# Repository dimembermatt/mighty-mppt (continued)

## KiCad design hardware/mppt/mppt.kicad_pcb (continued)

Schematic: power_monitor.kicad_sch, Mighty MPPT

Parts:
C801, C802: 100n; C_0402_1005Metric_Pad0.74x0.62mm_HandSolder
IC801: INA229AIDGSR; ti_INA229_AIDGSR
NT801: NetTie_2; NetTie-2_SMD_Pad0.5mm
R801: 86.6k; R_0603_1608Metric_Pad0.98x0.95mm_HandSolder
R802: 100k; R_0603_1608Metric_Pad0.98x0.95mm_HandSolder
R803, R805: 15; R_0603_1608Metric
R804: 4m; R_Shunt_Vishay_WSKW0612
TP801, TP802: TestPoint_2Pole; TestPoint_2Pads_Pitch2.54mm_Drill0.8mm

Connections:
+3V3: C802.2, IC801.6 (VS); also elsewhere on the board
/MON_IN_CS: IC801.1 (CS); also elsewhere on the board
/MON_SPI_CIPO: IC801.4 (MISO); also elsewhere on the board
/MON_SPI_CLK: IC801.5 (SCLK); also elsewhere on the board
/MON_SPI_COPI: IC801.2 (MOSI); also elsewhere on the board
/VI+: R804.1; also elsewhere on the board
/VI-: NT801.1, R802.2, TP801.2; also elsewhere on the board
/power_converter/Load Switch Source/I+: R801.1, R804.4; also elsewhere on the board
/power_converter/Power Monitor Source/IN+: C801.2, IC801.10 (IN+), R803.1, TP802.1
/power_converter/Power Monitor Source/IN-: C801.1, IC801.9 (IN-), R805.1, TP802.2
/power_converter/Power Monitor Source/VBUS: IC801.8 (VBUS), R801.2, R802.1, TP801.1
/power_converter/~MON_ALERT: IC801.3 (ALERT); also elsewhere on the board
GND: C802.1, IC801.7 (GND), NT801.2; also elsewhere on the board
unnamed: R803.2, R804.2
unnamed: R804.3, R805.2

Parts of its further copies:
C1301, C1302: 100n; C_0402_1005Metric_Pad0.74x0.62mm_HandSolder
IC1301: INA229AIDGSR; ti_INA229_AIDGSR
NT1301: NetTie_2; NetTie-2_SMD_Pad0.5mm
R1301: 86.6k; R_0603_1608Metric_Pad0.98x0.95mm_HandSolder
R1302: 100k; R_0603_1608Metric_Pad0.98x0.95mm_HandSolder
R1303, R1305: 15; R_0603_1608Metric
R1304: 4m; R_Shunt_Vishay_WSKW0612
TP1301, TP1302: TestPoint_2Pole; TestPoint_2Pads_Pitch2.54mm_Drill0.8mm

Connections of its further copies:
+3V3: C1302.2, IC1301.6 (VS); also elsewhere on the board
/MON_OUT_CS: IC1301.1 (CS); also elsewhere on the board
/MON_SPI_CIPO: IC1301.4 (MISO); also elsewhere on the board
/MON_SPI_CLK: IC1301.5 (SCLK); also elsewhere on the board
/MON_SPI_COPI: IC1301.2 (MOSI); also elsewhere on the board
/power_converter/Load Switch Sink/I-: R1301.1, R1304.1; also elsewhere on the board
/power_converter/OUT+: R1304.4; also elsewhere on the board
/power_converter/OUT-: NT1301.1, R1302.2, TP1301.2; also elsewhere on the board
/power_converter/Power Monitor Sink/IN+: C1301.2, IC1301.10 (IN+), R1303.1, TP1302.1
/power_converter/Power Monitor Sink/IN-: C1301.1, IC1301.9 (IN-), R1305.1, TP1302.2
/power_converter/Power Monitor Sink/VBUS: IC1301.8 (VBUS), R1301.2, R1302.1, TP1301.1
/power_converter/~MON_ALERT: IC1301.3 (ALERT); also elsewhere on the board
GND: C1302.1, IC1301.7 (GND), NT1301.2; also elsewhere on the board
unnamed: R1303.2, R1304.2
unnamed: R1304.3, R1305.2

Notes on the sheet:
0-150V 158.61V max rating
106kHz -3dB cutoff
0-10.24A 15.8A max power rating

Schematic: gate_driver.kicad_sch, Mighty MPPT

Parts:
C1001, C1003, C1004: 10u; C_1206_3216Metric_Pad1.33x1.80mm_HandSolder
C1002, C1005, C1006: 100n; C_0402_1005Metric_Pad0.74x0.62mm_HandSolder
D1001, D1003: Schottky; D_SOD-123F
D1002, D1005: Zener; D_SOD-123F
D1004: 0.62V; D_SMA
NT1001: NetTie_2; NetTie-2_SMD_Pad0.5mm
Q1001: Q_NMOS_GDS; SOT-223-3_TabPin2
R1001: 100k; R_0603_1608Metric_Pad0.98x0.95mm_HandSolder
R1002, R1003, R1004, R1005: 0; R_0805_2012Metric_Pad1.20x1.40mm_HandSolder
R1006: 1.5; R_1210_3225Metric_Pad1.30x2.65mm_HandSolder
R1007: R_DT; R_0805_2012Metric_Pad1.20x1.40mm_HandSolder
U1001: ADUM4221-1ARIZ; ad_ADUM4221_1ARIZ

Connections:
+3V3: C1001.1, C1002.1, R1001.1, U1001.3 (VDD1), U1001.8 (VDD1); also elsewhere on the board
+5V: C1004.1, C1006.1, D1004.2 (A), U1001.11 (VDDB); also elsewhere on the board
/power_converter/Gate Driver/CONV_EN: Q1001.1 (G); also elsewhere on the board
/power_converter/Gate Driver/CONV_PWM: U1001.1 (PWM); also elsewhere on the board
/power_converter/Gate Driver/DISABLE: Q1001.2 (D), R1001.2, U1001.5 (DISABLE)
/power_converter/Gate Driver/DT: R1007.2, U1001.6 (DT)
/power_converter/Gate Driver/VDDA: C1003.1, C1005.1, R1006.2, U1001.16 (VDDA)
/power_converter/Gate Driver/VOA: D1003.1 (K), R1004.1, U1001.15 (VOA)
/power_converter/Gate Driver/VOB: D1001.1 (K), R1002.1, U1001.10 (VOB)
/power_converter/SWH: D1005.1 (K), R1004.2; also elsewhere on the board
/power_converter/SWL: D1002.1 (K), R1002.2; also elsewhere on the board
/power_converter/VSW: C1003.2, C1005.2, D1005.2 (A), R1005.2, U1001.14 (GNDA); also elsewhere on the board
GND: C1001.2, C1002.2, NT1001.1, Q1001.3 (S), R1007.1, U1001.4 (GND1); also elsewhere on the board
GNDPWR: C1004.2, C1006.2, D1002.2 (A), NT1001.2, R1003.2, U1001.9 (GNDB); also elsewhere on the board
unnamed: D1001.2 (A), R1003.1
unnamed: D1003.2 (A), R1005.1
unnamed: D1004.1 (K), R1006.1

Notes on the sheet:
Determine this from 0.1.0rc breakout.
Target boost range @ 55kHz Max duty: 16V to 134V D = 1 - 1/150 = 0.8806 Min duty: 75V to 80V D = 1 - 75/80 = 0.0625 T_Hmin = (1 - 0.8806) / 55kHz - 20ns = 2150.9ns T_Lmax = 0.8806 / 55kHz + 20ns = 16030.9ns T_Lmin = 0.0625 / 55kHz + 20ns = 1156.36ns Q_CB (bootstrap capacitor charge) = 7.5nC + (1603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
Overkill fet selected to consolidate BOM, consider selecting smaller and cheaper one.

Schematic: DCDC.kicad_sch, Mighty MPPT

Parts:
C501, C505: 100n; C_0805_2012Metric
C502, C506: 1u; C_2220_5750Metric
C503, C507: 2.2u; C_2220_5750Metric
C504, C508, C509: 18u; C_Radial_D10.0mm_H16.0mm_P5.00mm
D501, D503: 150; D_SMA
D502: SMAJ150CA; D_SMA
L501: 471u; ferroxcube_PQ32_20_3C97_wire
LB501: CPV-PQ32/20-1S-12PD-Z; ferroxcube_CPV-PQ32_20-1S-12P-Z
LC501: PQ32/20-3C97
LH501: CLM/P-PQ32/20
NT501: NetTie_3_Tee; NetTie-3_SMD_Pad2.0mm
Q501, Q502: EPC2059; epc_EPC2059
TP501, TP502, TP505, TP506, TP507: TestPoint; TestPoint_Keystone_5000-5004_Miniature
TP503, TP504: TestPoint_2Pole; TestPoint_2Pads_Pitch2.54mm_Drill0.8mm

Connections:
/VI-: C501.2, C502.2, C503.2, C504.2, D501.2 (A), NT501.1; also elsewhere on the board
/power_converter/Active Load Sink/V+: C505.1, C506.1, C507.1, C508.1, C509.1, D503.1 (K), Q502.3 (D), Q502.5 (D), TP504.2, TP507.1; also elsewhere on the board
/power_converter/Active Load Source/V+: C501.1, C502.1, C503.1, C504.1, D501.1 (K), L501.1, TP501.1; also elsewhere on the board
/power_converter/OUT-: C505.2, C506.2, C507.2, C508.2, C509.2, D502.1 (A1), D503.2 (A), NT501.3, Q501.2 (S), Q501.4 (S), Q501.6 (S), TP503.1, TP505.1; also elsewhere on the board
/power_converter/SWH: Q502.1 (G), TP506.1; also elsewhere on the board
/power_converter/SWL: Q501.1 (G), TP502.1; also elsewhere on the board
/power_converter/VSW: D502.2 (A2), L501.2, Q501.3 (D), Q501.5 (D), Q502.2 (S), Q502.4 (S), Q502.6 (S), TP503.2, TP504.1; also elsewhere on the board
GNDPWR: NT501.2; also elsewhere on the board

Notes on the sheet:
TRANSIENT PROTECTION
HIGH SIDE FET
SWITCH NODE
LOW SIDE FET
OUTPUT CAPACITANCE
OUTPUT RETURN
Switch selected: EPC2059 with an optimal switching frequency of 55000 Hz Input capacitors selected: Bulk caps: A759MS186M2CAAE090 x 1 HF cap: CGA9P3X7T2E225M250KA x 1 Output capacitors selected: Bulk caps: A759MS186M2CAAE090 x 2 HF cap: CGA9P3X7T2E225M250KA x 1 Input inductor selected: PQ32/20-3C97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
INPUT CAPACITANCE
OVP
OCP
INPUT
Is this sized appropriately to protect 170VDS rated FETs?
INDUCTANCE
OUTPUT
INPUT RETURN
HF Loop

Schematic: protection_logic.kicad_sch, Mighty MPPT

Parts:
C901, C902, C903, C904: 100n; C_0402_1005Metric_Pad0.74x0.62mm_HandSolder
IC901: SN74LVC08APWR; ti_SN74LVC08A_PWR
IC902: SN74LVC1G04DBVR; ti_SN74LVC1G04_DBVR
IC903: SN74HCS367PWR; ti_SN74HCS367_PWR
IC904: SN74LVC2G32DCUR; ti_SN74LVC2G32_DCUR
R901, R902, R903, R904, R905, R906, R907: 100k; R_0603_1608Metric_Pad0.98x0.95mm_HandSolder
TP901, TP902, TP903, TP904, TP905, TP906: TestPoint_Small; TestPoint_Pad_D1.0mm

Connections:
+3V3: C901.1, C902.1, C903.1, C904.1, IC901.14 (VCC), IC902.5 (VCC), IC903.16 (VCC), IC904.8 (VCC), R901.1, R902.1, R904.1; also elsewhere on the board
/AL_IN_EN: IC904.2 (1B); also elsewhere on the board
/AL_OUT_EN: IC904.6 (2B); also elsewhere on the board
/CONV_DISABLE: IC903.15 (~2OE); also elsewhere on the board
/CONV_EN: IC901.10 (3B); also elsewhere on the board
/CONV_PWM: IC903.14 (2A2); also elsewhere on the board
/LS_IN_EN: IC901.2 (1B); also elsewhere on the board
/LS_OUT_EN: IC901.5 (2B); also elsewhere on the board
/MON_ALERT: IC902.4 (Y), IC904.1 (1A), IC904.5 (2A); also elsewhere on the board
/PROT_DISABLE: IC903.1 (~1OE); also elsewhere on the board
/power_converter/AL_SNK_EN_BUF: IC903.9 (1Y4), R902.2, TP901.1; also elsewhere on the board
/power_converter/AL_SRC_EN_BUF: IC903.7 (1Y3), R904.2, TP903.1; also elsewhere on the board
/power_converter/Gate Driver/CONV_EN: IC903.11 (2Y1), R906.1, TP905.1; also elsewhere on the board
/power_converter/Gate Driver/CONV_PWM: IC903.13 (2Y2), R907.1, TP906.1; also elsewhere on the board
/power_converter/LS_SNK_EN_BUF: IC903.5 (1Y2), R905.1, TP904.1; also elsewhere on the board
/power_converter/LS_SRC_EN_BUF: IC903.3 (1Y1), R903.1, TP902.1; also elsewhere on the board
/power_converter/Protection Logic/AL_SNK_EN_OR: IC903.10 (1A4), IC904.7 (1Y)
/power_converter/Protection Logic/AL_SRC_EN_OR: IC903.6 (1A3), IC904.3 (2Y)
/power_converter/Protection Logic/CONV_EN_AND: IC901.8 (3Y), IC903.12 (2A1)
/power_converter/Protection Logic/LS_SNK_EN_AND: IC901.6 (2Y), IC903.4 (1A2)
/power_converter/Protection Logic/LS_SRC_EN_AND: IC901.3 (1Y), IC903.2 (1A1)
/power_converter/~MON_ALERT: IC901.1 (1A), IC901.4 (2A), IC901.9 (3A), IC902.2 (A), R901.2; also elsewhere on the board
GND: C901.2, C902.2, C903.2, C904.2, IC901.7 (GND), IC901.11 (4Y), IC901.12 (4A), IC901.13 (4B), IC902.3 (GND), IC903.8 (GND), IC904.4 (GND), R903.2, R905.2, R906.2, R907.2; also elsewhere on the board

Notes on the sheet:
DISABLE used for logic testing. Tie to GND for final design.
Schmitt Trigger Buffer.
OR logic.
AND logic.
Open drain wired-OR.
NOT logic.

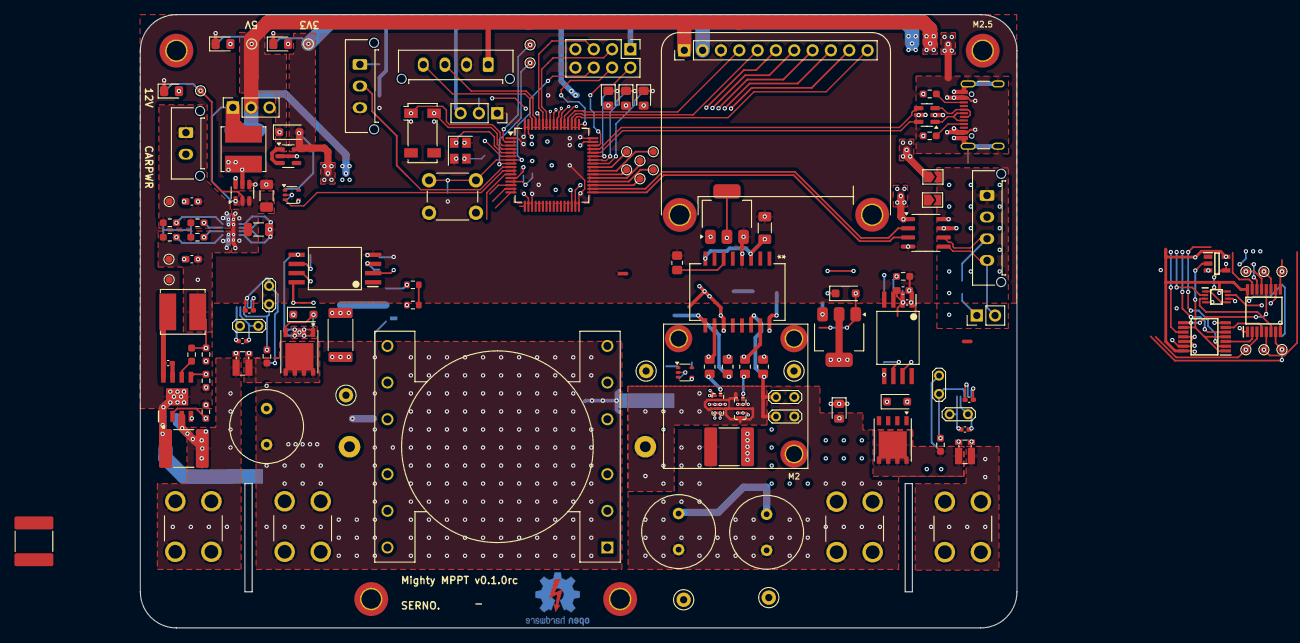
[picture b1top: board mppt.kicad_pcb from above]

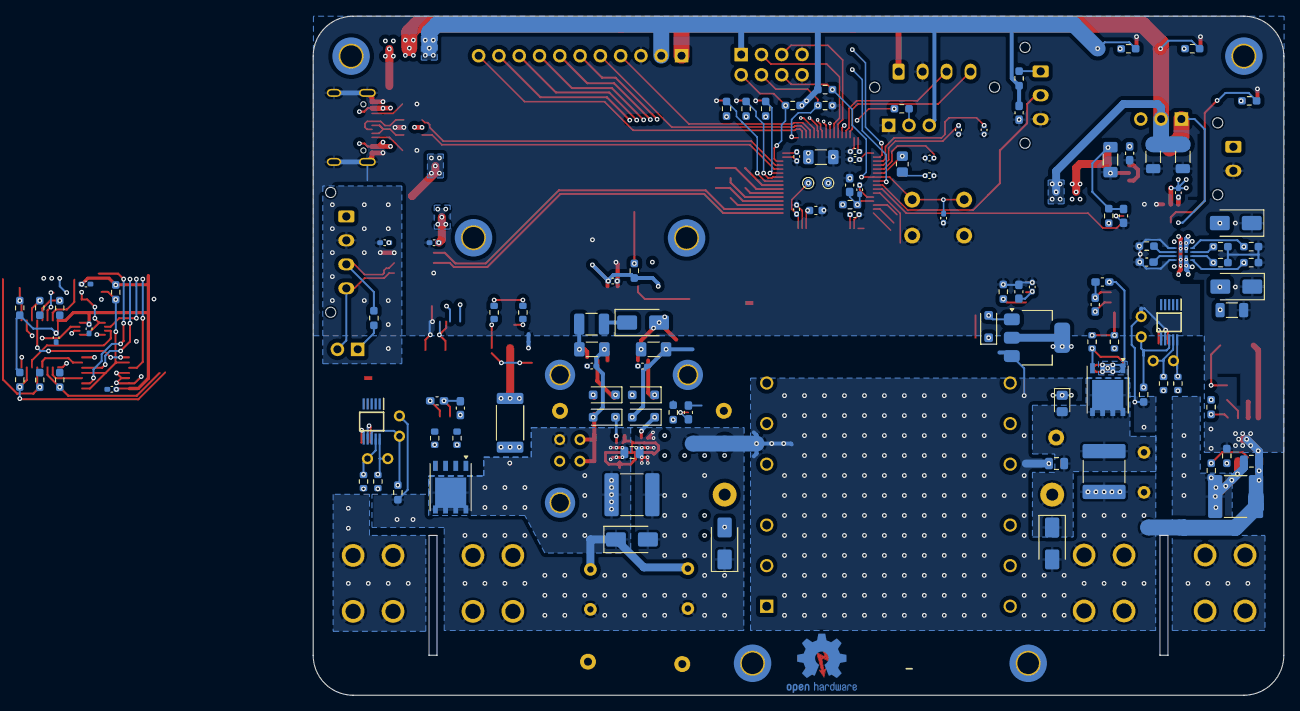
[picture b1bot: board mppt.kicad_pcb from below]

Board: 4 copper layers, 121.5 x 85.0 mm, 257 parts (119 on the bottom side), 161 nets.

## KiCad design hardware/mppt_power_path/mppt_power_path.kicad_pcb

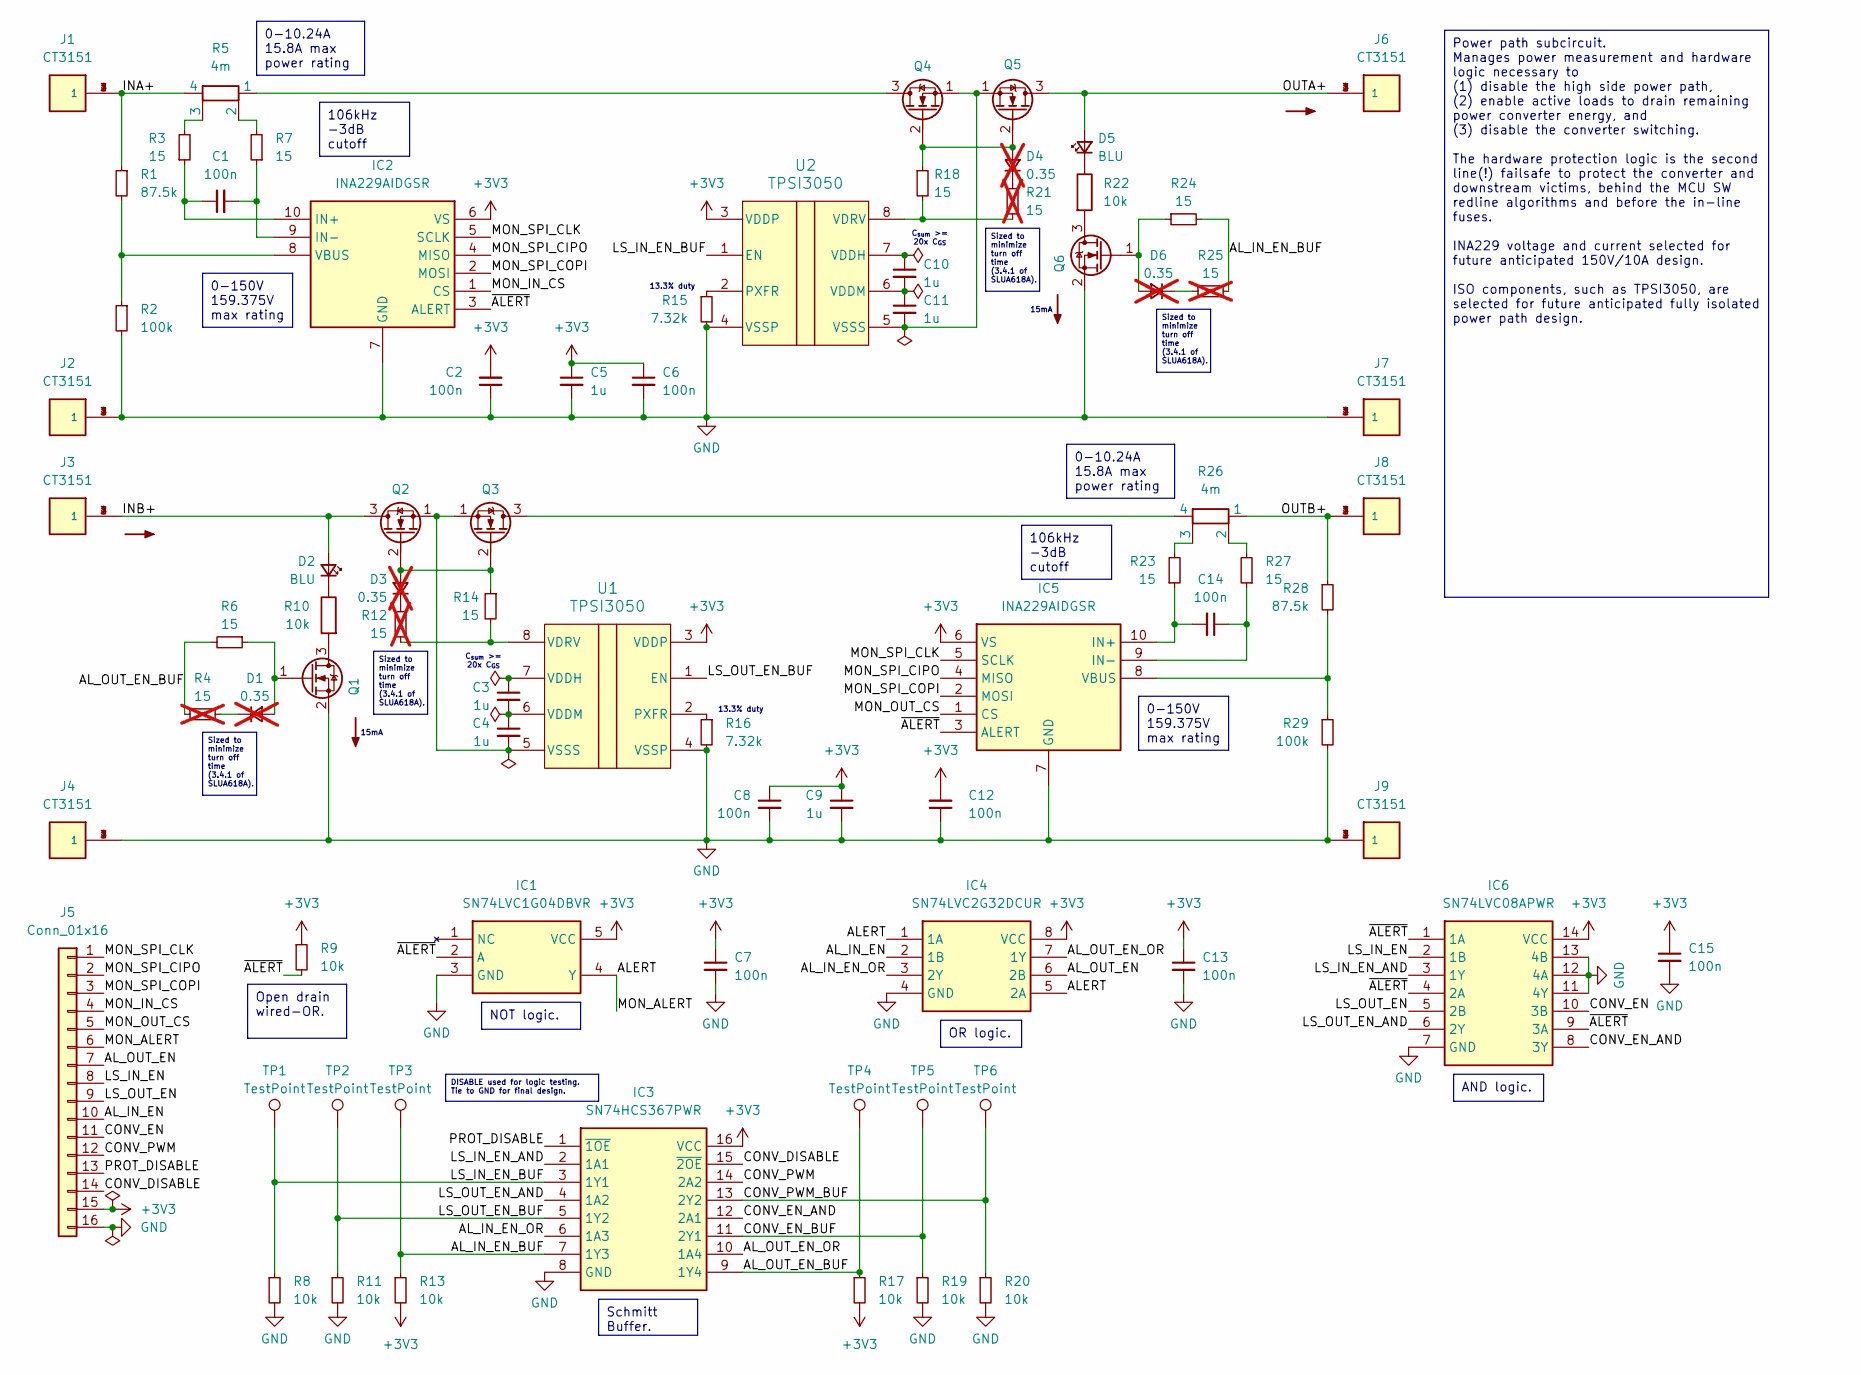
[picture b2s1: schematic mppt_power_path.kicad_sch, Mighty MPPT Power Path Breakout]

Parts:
C1, C2, C6, C7, C8, C12, C13, C14, C15: 100n; C_0805_2012Metric_Pad1.18x1.45mm_HandSolder
C3, C4, C5, C9, C10, C11: 1u; C_0805_2012Metric_Pad1.18x1.45mm_HandSolder
D1, D3, D4, D6: 0.35; D_SOD-123F; not fitted
D2, D5: BLU; LED_0805_2012Metric_Pad1.15x1.40mm_HandSolder
IC1: SN74LVC1G04DBVR; ti_SN74LVC1G04_DBVR
IC2, IC5: INA229AIDGSR; ti_INA229_AIDGSR
IC3: SN74HCS367PWR; ti_SN74HCS367_PWR
IC4: SN74LVC2G32DCUR; ti_SN74LVC2G32_DCUR
IC6: SN74LVC08APWR; ti_SN74LVC08A_PWR
J1, J2, J3, J4, J6, J7, J8, J9: CT3151; caltest_ct3151
J5: Conn_01x16; PinHeader_1x16_P2.54mm_Vertical
Q1, Q6: Q_NMOS_GSD; SOT-23-3
Q2, Q3, Q4, Q5: Q_NMOS_SGD; PowerPAK_SO-8_Single
R1, R28: 87.5k; R_0805_2012Metric_Pad1.20x1.40mm_HandSolder
R2, R29: 100k; R_0805_2012Metric_Pad1.20x1.40mm_HandSolder
R3, R6, R7, R14, R18, R23, R24, R27: 15; R_0805_2012Metric_Pad1.20x1.40mm_HandSolder
R4, R12, R21, R25: 15; R_0805_2012Metric_Pad1.20x1.40mm_HandSolder; not fitted
R5, R26: 4m; R_Shunt_Vishay_WSKW0612
R8, R9, R11, R13, R17, R19, R20: 10k; R_0805_2012Metric_Pad1.20x1.40mm_HandSolder
R10, R22: 10k; R_2512_6332Metric_Pad1.40x3.35mm_HandSolder
R15, R16: 7.32k; R_0805_2012Metric_Pad1.20x1.40mm_HandSolder
TP1, TP2, TP3, TP4, TP5, TP6: TestPoint; TestPoint_Keystone_5000-5004_Miniature
U1, U2: TPSI3050; ti_TPS3050_DWZ

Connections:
+3V3: C2.2, C5.1, C6.1, C7.1, C8.1, C9.1, C12.2, C13.1, C15.1, IC1.5 (VCC), IC2.6 (VS), IC3.16 (VCC), IC4.8 (VCC), IC5.6 (VS), IC6.14 (VCC), J5.15, R9.1, R13.2, R17.2, U1.3 (VDDP), U2.3 (VDDP)
/ALERT: IC1.4 (Y), IC4.1 (1A), IC4.5 (2A), J5.6
/AL_IN_EN: IC4.2 (1B), J5.10
/AL_IN_EN_BUF: IC3.7 (1Y3), R13.1, R24.2, R25.2, TP3.1
/AL_IN_EN_OR: IC3.6 (1A3), IC4.3 (2Y)
/AL_OUT_EN: IC4.6 (2B), J5.7
/AL_OUT_EN_BUF: IC3.9 (1Y4), R4.2, R6.2, R17.1, TP4.1
/AL_OUT_EN_OR: IC3.10 (1A4), IC4.7 (1Y)
/CONV_DISABLE: IC3.15 (~2OE), J5.14
/CONV_EN: IC6.10 (3B), J5.11
/CONV_EN_AND: IC3.12 (2A1), IC6.8 (3Y)
/CONV_EN_BUF: IC3.11 (2Y1), R19.1, TP5.1
/CONV_PWM: IC3.14 (2A2), J5.12
/CONV_PWM_BUF: IC3.13 (2Y2), R20.1, TP6.1
/INA+: J1.1, J1.2 (1), J1.3 (1), J1.4 (1), R1.1, R5.4
/INB+: D2.2 (A), J3.1, J3.2 (1), J3.3 (1), J3.4 (1), Q2.3 (D)
/LS_IN_EN: IC6.2 (1B), J5.8
/LS_IN_EN_AND: IC3.2 (1A1), IC6.3 (1Y)
/LS_IN_EN_BUF: IC3.3 (1Y1), R8.1, TP1.1, U2.1 (EN)
/LS_OUT_EN: IC6.5 (2B), J5.9
/LS_OUT_EN_AND: IC3.4 (1A2), IC6.6 (2Y)
/LS_OUT_EN_BUF: IC3.5 (1Y2), R11.1, TP2.1, U1.1 (EN)
/MON_IN_CS: IC2.1 (CS), J5.4
/MON_OUT_CS: IC5.1 (CS), J5.5
/MON_SPI_CIPO: IC2.4 (MISO), IC5.4 (MISO), J5.2
/MON_SPI_CLK: IC2.5 (SCLK), IC5.5 (SCLK), J5.1
/MON_SPI_COPI: IC2.2 (MOSI), IC5.2 (MOSI), J5.3
/OUTA+: D5.2 (A), J6.1, J6.2 (1), J6.3 (1), J6.4 (1), Q5.3 (D)
/OUTB+: J8.1, J8.2 (1), J8.3 (1), J8.4 (1), R26.1, R28.1
/PROT_DISABLE: IC3.1 (~1OE), J5.13
/~ALERT: IC1.2 (A), IC2.3 (ALERT), IC5.3 (ALERT), IC6.1 (1A), IC6.4 (2A), IC6.9 (3A), R9.2
GND: C2.1, C5.2, C6.2, C7.2, C8.2, C9.2, C12.1, C13.2, C15.2, IC1.3 (GND), IC2.7 (GND), IC3.8 (GND), IC4.4 (GND), IC5.7 (GND), IC6.7 (GND), IC6.11 (4Y), IC6.12 (4A), IC6.13 (4B), J2.1, J2.2 (1), J2.3 (1), J2.4 (1), J4.1, J4.2 (1), J4.3 (1), J4.4 (1), J5.16, J7.1, J7.2 (1), J7.3 (1), J7.4 (1), J9.1, J9.2 (1), J9.3 (1), J9.4 (1), Q1.2 (S), Q6.2 (S), R2.2, R8.2, R11.2, R15.2, R16.2, R19.2, R20.2, R29.2, U1.4 (VSSP), U2.4 (VSSP)
unnamed: D1.2 (A), Q1.1 (G), R6.1
unnamed: D1.1 (K), R4.1
unnamed: D2.1 (K), R10.1
unnamed: D3.2 (A), Q2.2 (G), Q3.2 (G), R14.1
unnamed: D3.1 (K), R12.1
unnamed: D4.2 (A), Q4.2 (G), Q5.2 (G), R18.1
unnamed: D4.1 (K), R21.1
unnamed: D5.1 (K), R22.1
unnamed: D6.2 (A), Q6.1 (G), R24.1
unnamed: D6.1 (K), R25.1
unnamed: C1.1, IC2.10 (IN+), R3.1
unnamed: C1.2, IC2.9 (IN-), R7.1
unnamed: IC2.8 (VBUS), R1.2, R2.1
unnamed: C14.2, IC5.10 (IN+), R23.1
unnamed: C14.1, IC5.9 (IN-), R27.1
unnamed: IC5.8 (VBUS), R28.2, R29.1
unnamed: Q1.3 (D), R10.2
unnamed: C4.2, Q2.1 (S), Q3.1 (S), U1.5 (VSSS)
unnamed: Q3.3 (D), R26.4
unnamed: Q4.3 (D), R5.1
unnamed: C11.2, Q4.1 (S), Q5.1 (S), U2.5 (VSSS)
unnamed: Q6.3 (D), R22.2
unnamed: R3.2, R5.3
unnamed: R5.2, R7.2
unnamed: R23.2, R26.3
unnamed: R26.2, R27.2
unnamed: R16.1, U1.2 (PXFR)
unnamed: C3.1, U1.7 (VDDH)
unnamed: C3.2, C4.1, U1.6 (VDDM)
unnamed: R12.2, R14.2, U1.8 (VDRV)
unnamed: R15.1, U2.2 (PXFR)
unnamed: C10.1, U2.7 (VDDH)
unnamed: C10.2, C11.1, U2.6 (VDDM)
unnamed: R18.2, R21.2, U2.8 (VDRV)

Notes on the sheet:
Sized to minimize turn off time (3.4.1 of SLUA618A).
0-150V 159.375V max rating
0-10.24A 15.8A max power rating
NOT logic.
Schmitt Buffer.
Open drain wired-OR.
106kHz -3dB cutoff
Power path subcircuit. Manages power measurement and hardware logic necessary to (1) disable the high side power path, (2) enable active loads to drain remaining power converter energy, and (3) disable the converter switching. The hardware protection logic is the second line(!) failsafe to protect 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
OR logic.
AND logic.
DISABLE used for logic testing. Tie to GND for final design.
C_{sum} >= 20x C_{GS}
13.3% duty
15mA

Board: 2 copper layers, 79 parts (4 on the bottom side), 66 nets, no tracks yet.

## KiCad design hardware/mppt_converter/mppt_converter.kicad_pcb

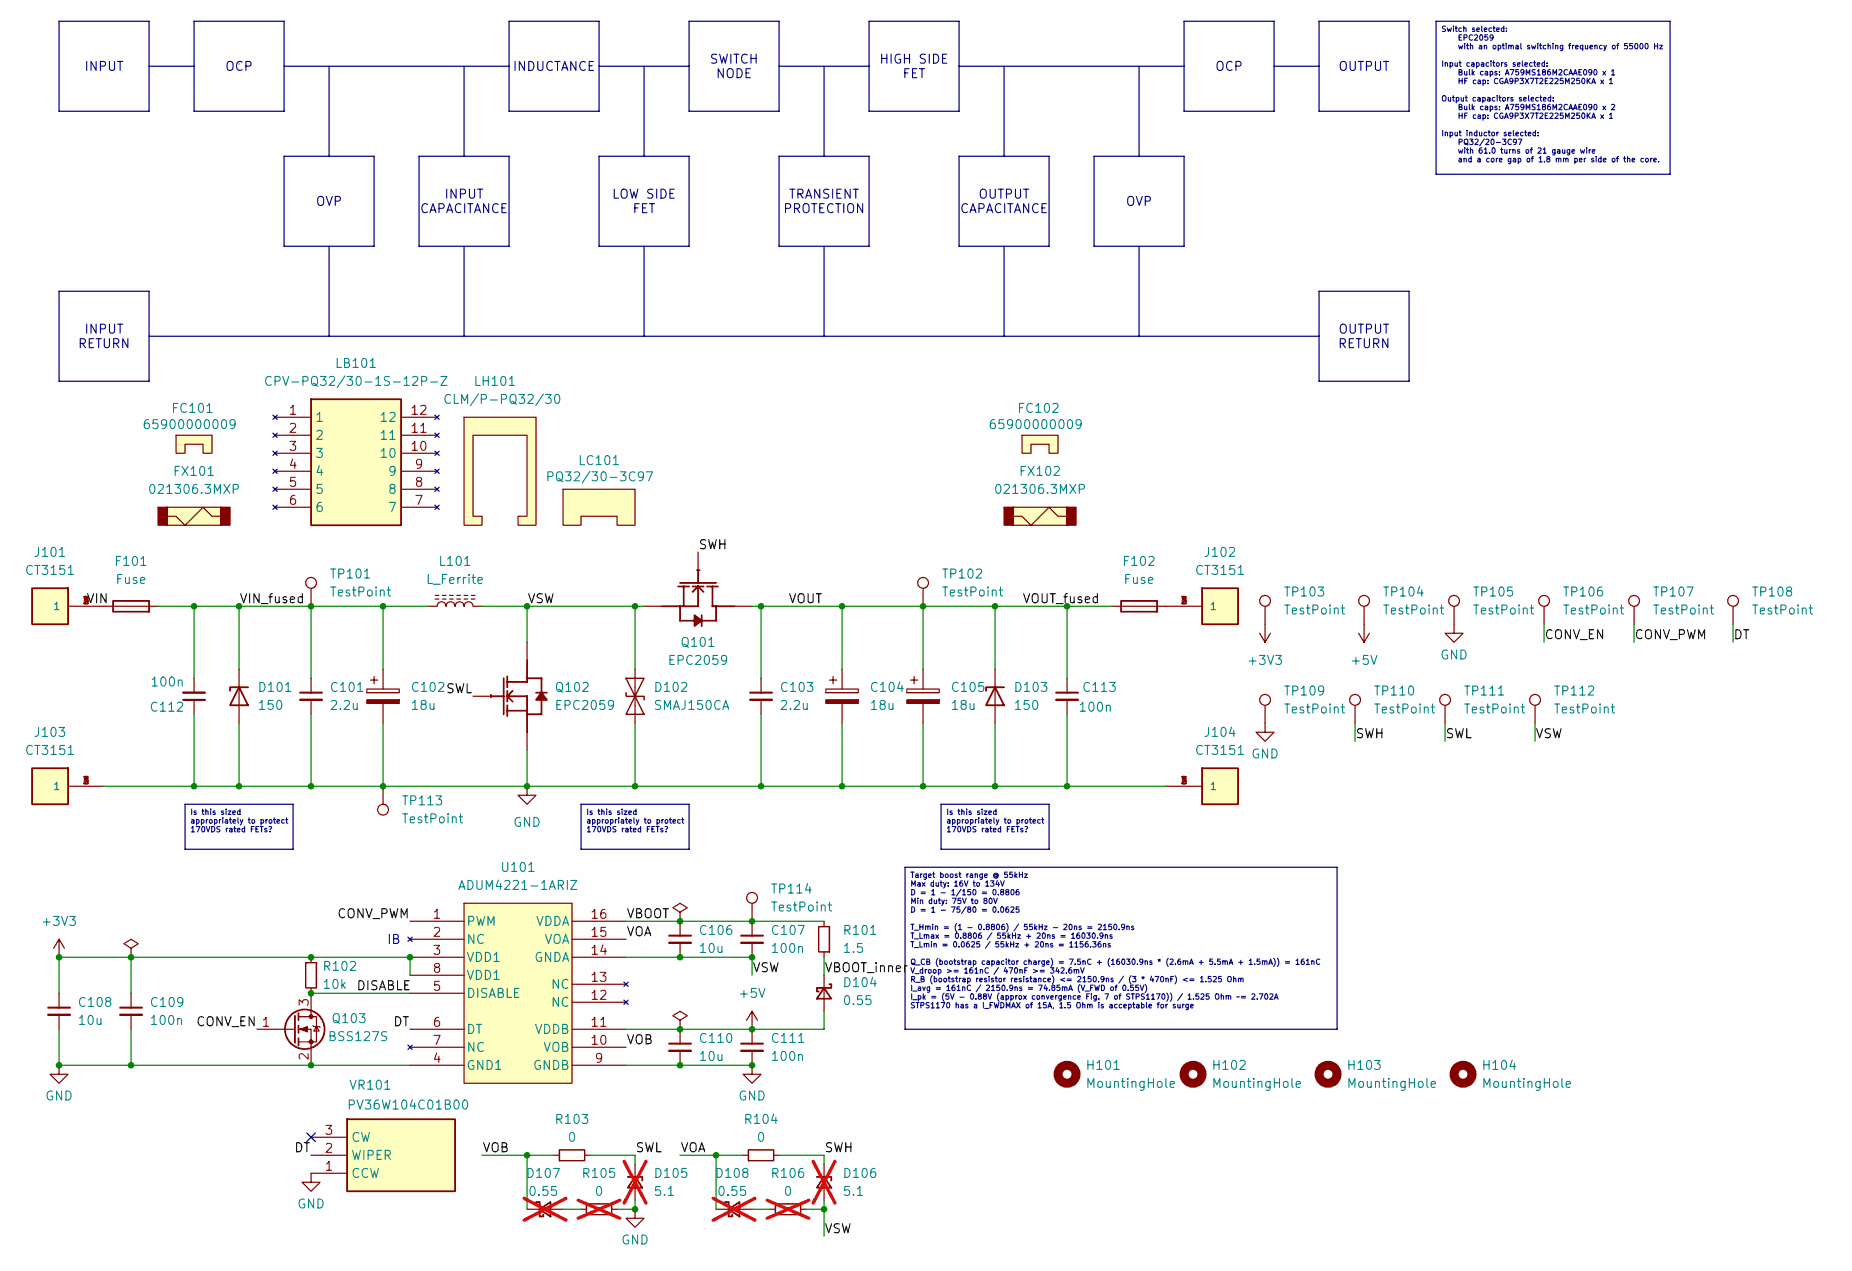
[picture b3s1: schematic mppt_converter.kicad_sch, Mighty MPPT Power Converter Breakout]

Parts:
C101, C103: 2.2u; C_2220_5750Metric_Pad1.97x5.40mm_HandSolder
C102, C104, C105: 18u; C_Radial_D10.0mm_H16.0mm_P5.00mm
C106, C108, C110: 10u; C_0805_2012Metric_Pad1.18x1.45mm_HandSolder
C107, C109, C111, C112, C113: 100n; C_0805_2012Metric_Pad1.18x1.45mm_HandSolder
D101, D103: 150; D_SMA
D102: SMAJ150CA; D_SMA
D104: 0.55; stm_STPS1170AF
D105, D106: 5.1; D_SOD-123; not fitted
D107, D108: 0.55; stm_STPS1170AF; not fitted
F101, F102: Fuse; littelfuse_65600001009
FC101, FC102: 65900000009
FX101, FX102: 021306.3MXP
H101, H102, H103, H104: MountingHole; MountingHole_5.3mm_M5
J101, J102, J103, J104: CT3151; caltest_ct3151
L101: L_Ferrite; ferroxcube_PQ32_30_3C97_wire
LB101: CPV-PQ32/30-1S-12P-Z; ferroxcube_CPV-PQ32_30-1S-12P-Z
LC101: PQ32/30-3C97
LH101: CLM/P-PQ32/30
Q101, Q102: EPC2059; epc_EPC2059
Q103: BSS127S; SOT-23
R101: 1.5; R_0805_2012Metric_Pad1.20x1.40mm_HandSolder
R102: 10k; R_0805_2012Metric_Pad1.20x1.40mm_HandSolder
R103, R104: 0; R_0805_2012Metric_Pad1.20x1.40mm_HandSolder
R105, R106: 0; R_0805_2012Metric_Pad1.20x1.40mm_HandSolder; not fitted
TP101, TP102, TP103, TP104, TP105, TP106, TP107, TP108, TP109, TP110, TP111, TP112, TP113, TP114: TestPoint; TestPoint_Keystone_5000-5004_Miniature
U101: ADUM4221-1ARIZ; ad_ADUM4221_1ARIZ
VR101: PV36W104C01B00; bourns_PV36W201C01B00

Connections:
+3V3: C108.1, C109.1, R102.1, TP103.1, U101.3 (VDD1), U101.8 (VDD1)
+5V: C110.1, C111.1, D104.2 (A), TP104.1, U101.11 (VDDB)
/CONV_EN: Q103.1 (G), TP106.1
/CONV_PWM: TP107.1, U101.1 (PWM)
/DISABLE: Q103.3 (D), R102.2, U101.5 (DISABLE)
/DT: TP108.1, U101.6 (DT), VR101.2 (WIPER)
/SWH: D106.1 (K), Q101.1 (G), R104.2, TP110.1
/SWL: D105.1 (K), Q102.1 (G), R103.2, TP111.1
/VBOOT: C106.1, C107.1, R101.2, TP114.1, U101.16 (VDDA)
/VBOOT_inner: D104.1 (K), R101.1
/VIN_fused: C101.1, C102.1, C112.2, D101.1 (K), F101.2, L101.1, TP101.1
/VOA: D108.1 (K), R104.1, U101.15 (VOA)
/VOB: D107.1 (K), R103.1, U101.10 (VOB)
/VOUT: C103.1, C104.1, C105.1, C113.1, D103.1 (K), F102.1, Q101.3 (D), Q101.5 (D), TP102.1
/VSW: C106.2, C107.2, D102.2 (A2), D106.2 (A), L101.2, Q101.2 (S), Q101.4 (S), Q101.6 (S), Q102.3 (D), Q102.5 (D), R106.2, TP112.1, U101.14 (GNDA)
GND: C101.2, C102.2, C103.2, C104.2, C105.2, C108.2, C109.2, C110.2, C111.2, C112.1, C113.2, D101.2 (A), D102.1 (A1), D103.2 (A), D105.2 (A), J103.1, J103.2 (1), J103.3 (1), J103.4 (1), J104.1, J104.2 (1), J104.3 (1), J104.4 (1), Q102.2 (S), Q102.4 (S), Q102.6 (S), Q103.2 (S), R105.2, TP105.1, TP109.1, TP113.1, U101.4 (GND1), U101.9 (GNDB), VR101.1 (CCW)
unnamed: D107.2 (A), R105.1
unnamed: D108.2 (A), R106.1
unnamed: F101.1, J101.1, J101.2 (1), J101.3 (1), J101.4 (1)
unnamed: F102.2, J102.1, J102.2 (1), J102.3 (1), J102.4 (1)

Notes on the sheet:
Switch selected: EPC2059 with an optimal switching frequency of 55000 Hz Input capacitors selected: Bulk caps: A759MS186M2CAAE090 x 1 HF cap: CGA9P3X7T2E225M250KA x 1 Output capacitors selected: Bulk caps: A759MS186M2CAAE090 x 2 HF cap: CGA9P3X7T2E225M250KA x 1 Input inductor selected: PQ32/20-3C97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
OUTPUT
OVP
TRANSIENT PROTECTION
OCP
OUTPUT CAPACITANCE
LOW SIDE FET
Is this sized appropriately to protect 170VDS rated FETs?
SWITCH NODE
Target boost range @ 55kHz Max duty: 16V to 134V D = 1 - 1/150 = 0.8806 Min duty: 75V to 80V D = 1 - 75/80 = 0.0625 T_Hmin = (1 - 0.8806) / 55kHz - 20ns = 2150.9ns T_Lmax = 0.8806 / 55kHz + 20ns = 16030.9ns T_Lmin = 0.0625 / 55kHz + 20ns = 1156.36ns Q_CB (bootstrap capacitor charge) = 7.5nC + (1603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
OUTPUT RETURN
HIGH SIDE FET
INDUCTANCE
INPUT CAPACITANCE
INPUT RETURN
INPUT

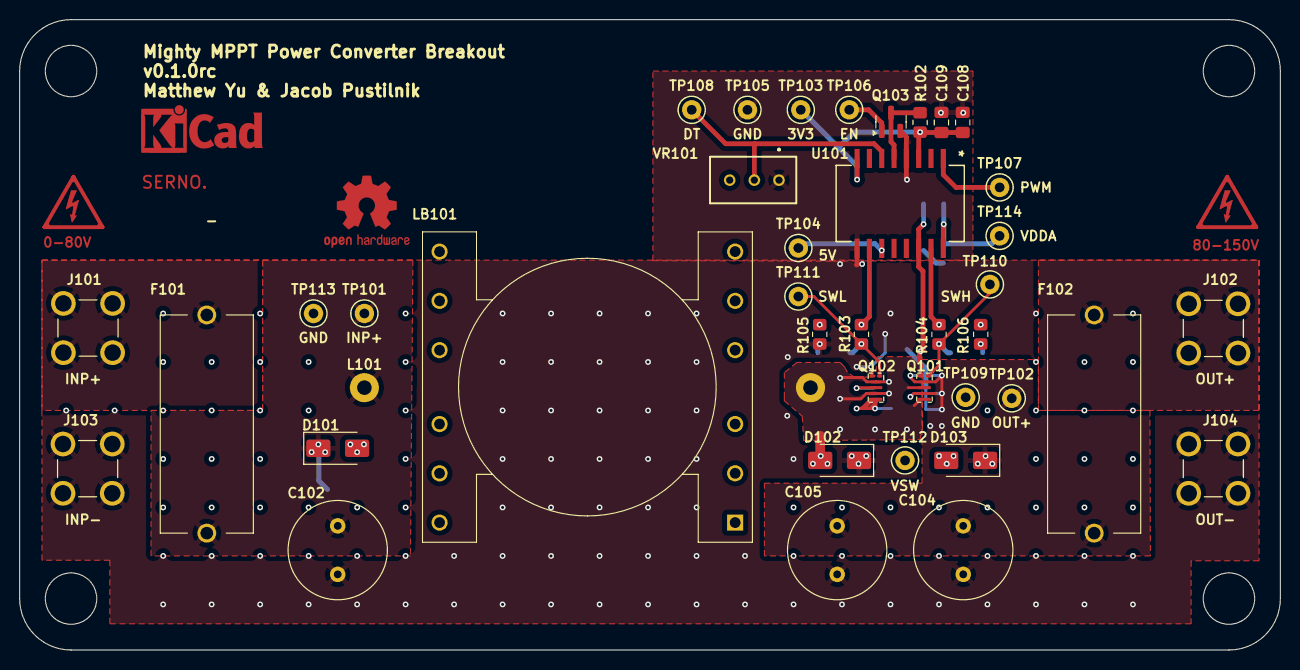
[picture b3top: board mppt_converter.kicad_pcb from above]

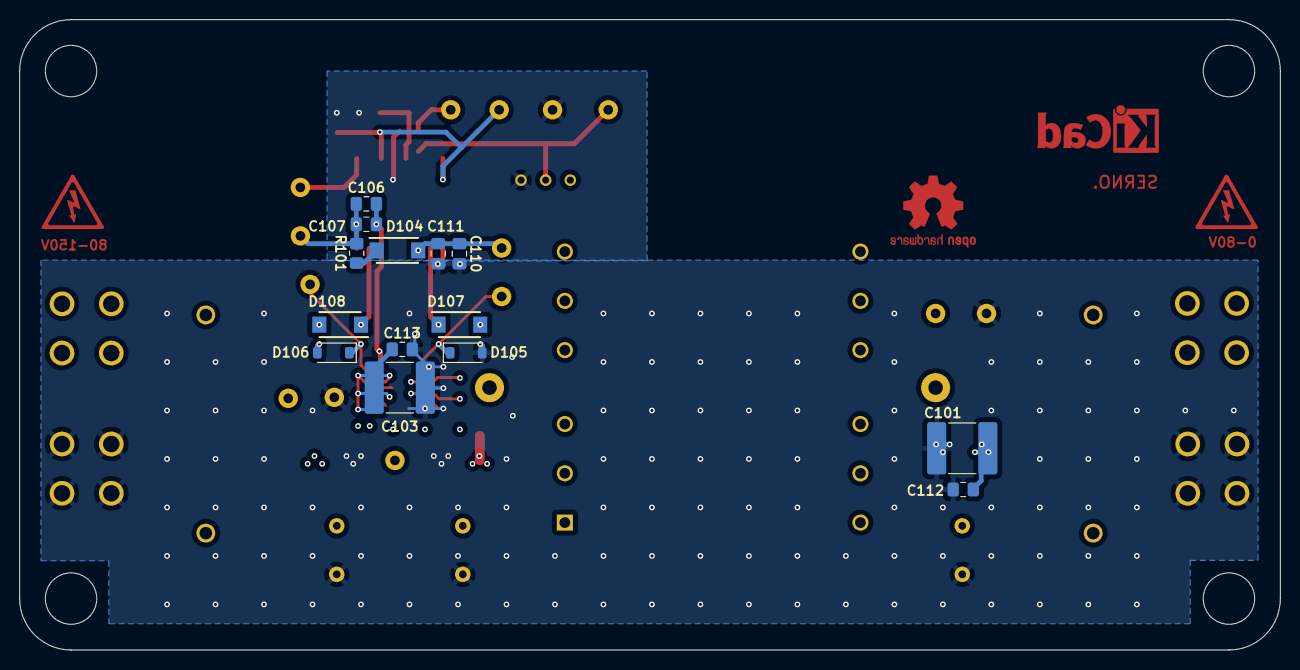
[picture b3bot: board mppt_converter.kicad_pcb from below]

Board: 4 copper layers, 130.0 x 65.0 mm, 58 parts (14 on the bottom side), 20 nets.
